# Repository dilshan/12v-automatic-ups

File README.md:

# 12V Uninterruptible Power Supply

This 12V uninterruptible power supply initially designs to drive my fiber optic modem/router. The key reason to build this power supply is to get continuous internet and phone connection during power failures. Core components of this power supply are a constant voltage charger, 12V DC power supply, AC line monitoring unit, and 12V high capacity sealed lead-acid battery. The entire system designs using locally available components.

The charging circuit of this system builds around using the popular *[LM350](https://www.ti.com/lit/ds/snvs772b/snvs772b.pdf)* voltage regulator. This regulator calibrates to provide both 14.4V fast charging and 13.6V trickle charging. Based on the condition of the battery, the MCU will determine the appropriate charging mode.

At the online state, the *[LM2576-12](https://www.ti.com/lit/ds/symlink/lm2576.pdf)* switching regulator provides 12V output to the driving system. (in my arrangement, a fiber optic router).

The *[PIC16F688](http://ww1.microchip.com/downloads/en/devicedoc/41203d.pdf)* MCU monitors the AC line and battery to controls the output voltage of the *LM350* regulator and the output relay. The firmware of this MCU written using the *[Microchip XC8](https://www.microchip.com/en-us/development-tools-tools-and-software/mplab-xc-compilers)* compiler, and all the source code and configuration files are available to [download](https://github.com/dilshan/12v-automatic-ups/releases) in this project repository.

The sealed 12V lead-acid battery is the most crucial component of this unit. 12V, 9Ah battery is the most recommended for this system. At the time of this writing, this battery cost around Rs. 3500 (US$ 17.60), and I bought it from a local online store.

In online mode, this system provides 12V output. In offline mode, if it has a fully charged battery, it delivers an output of 12.5V.

This uninterruptible power supply is suitable for appliances that need 12V - 13V input with a maximum of 2A current. With the configuration described above, this system continued to power my *[Huawei HG8245H5](https://carrier.huawei.com/en/products/fixed-network/access/cpe/h-series-products/hg8245h)* fiber optic router for more than 7 hours.

This power supply unit is an open hardware project. All the [schematic](https://github.com/dilshan/12v-automatic-ups/blob/main/design/ups-12v.pdf), [KiCAD PCB design files](https://github.com/dilshan/12v-automatic-ups/tree/main/design), [firmware source codes](https://github.com/dilshan/12v-automatic-ups/tree/main/firmware), and [compiled binaries](https://github.com/dilshan/12v-automatic-ups/releases) are available to download in this repository.

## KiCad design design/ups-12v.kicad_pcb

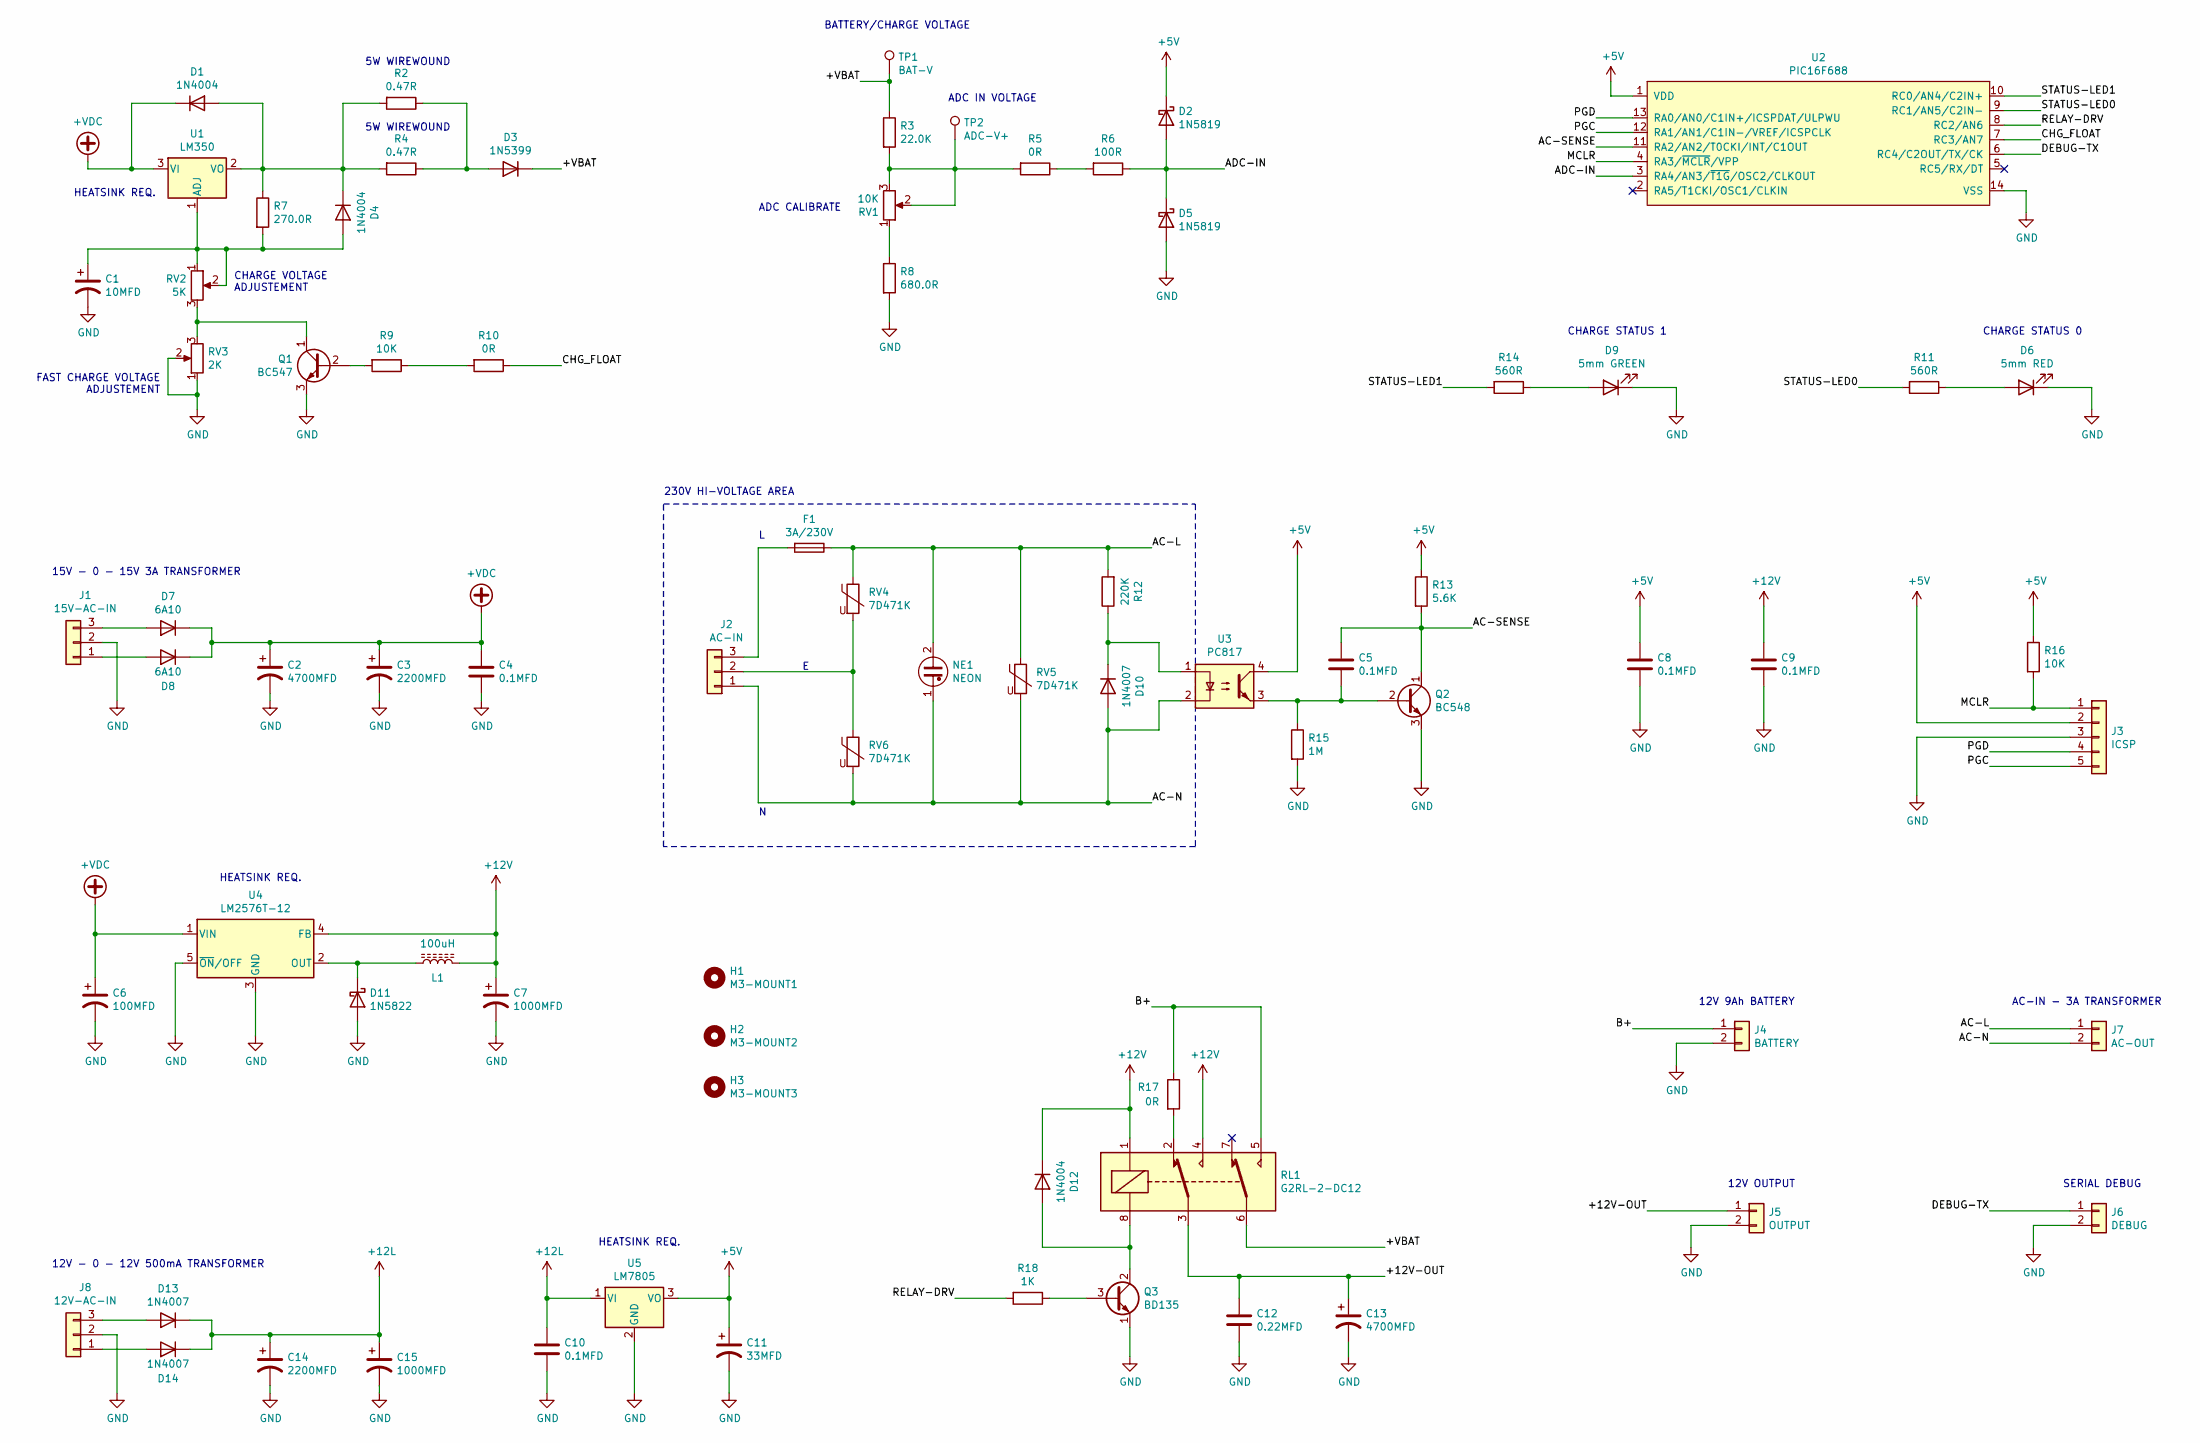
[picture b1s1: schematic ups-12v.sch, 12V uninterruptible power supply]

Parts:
C1: 10MFD; CP_Radial_D5.0mm_P2.00mm
C2, C13: 4700MFD; CP_Radial_D18.0mm_P7.50mm
C3, C14: 2200MFD; CP_Radial_D16.0mm_P7.50mm
C4, C5, C8, C9, C10: 0.1MFD; C_Disc_D10.5mm_W5.0mm_P7.50mm
C6: 100MFD; CP_Radial_D6.3mm_P2.50mm
C7, C15: 1000MFD; CP_Radial_D12.5mm_P5.00mm
C11: 33MFD; CP_Radial_D5.0mm_P2.50mm
C12: 0.22MFD; C_Disc_D11.0mm_W5.0mm_P10.00mm
D1, D4, D12: 1N4004; D_DO-41_SOD81_P10.16mm_Horizontal
D2, D5: 1N5819; D_DO-41_SOD81_P10.16mm_Horizontal
D3: 1N5399; D_DO-41_SOD81_P10.16mm_Horizontal
D6: 5mm RED; PinHeader_1x02_P2.54mm_Vertical
D7, D8: 6A10; D_P600_R-6_P20.00mm_Horizontal
D9: 5mm GREEN; PinHeader_1x02_P2.54mm_Vertical
D10, D13, D14: 1N4007; D_DO-41_SOD81_P10.16mm_Horizontal
D11: 1N5822; D_DO-201AD_P15.24mm_Horizontal
F1: 3A/230V; Fuseholder_Cylinder-5x20mm_Schurter_0031_8201_Horizontal_Op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
H1: M3-MOUNT1; MountingHole_3.2mm_M3
H2: M3-MOUNT2; MountingHole_3.2mm_M3
H3: M3-MOUNT3; MountingHole_3.2mm_M3
J1: 15V-AC-IN; Molex_Sabre_43160-0103_1x03_P7.49mm_Vertical
J2: AC-IN; Molex_Sabre_43160-0103_1x03_P7.49mm_Vertical
J3: ICSP; PinHeader_1x05_P2.54mm_Vertical
J4: BATTERY; Molex_Sabre_43160-0102_1x02_P7.49mm_Vertical
J5: OUTPUT; Molex_Sabre_43160-0102_1x02_P7.49mm_Vertical
J6: DEBUG; PinHeader_1x02_P2.54mm_Vertical
J7: AC-OUT; Molex_Sabre_43160-0102_1x02_P7.49mm_Vertical
J8: 12V-AC-IN; Molex_Sabre_43160-0103_1x03_P7.49mm_Vertical
L1: 100uH; L_Toroid_Vertical_L13.0mm_W6.5mm_P5.60mm
NE1: NEON; Fuse_Bourns_MF-RG300
Q1: BC547; TO-92_HandSolder
Q2: BC548; TO-92_HandSolder
Q3: BD135; TO-126-3_Vertical
R2, R4: 0.47R; R_Axial_Power_L25.0mm_W6.4mm_P27.94mm
R3: 22.0K; R_Axial_DIN0207_L6.3mm_D2.5mm_P10.16mm_Horizontal
R5: 0R; R_Axial_DIN0207_L6.3mm_D2.5mm_P15.24mm_Horizontal
R6: 100R; R_Axial_DIN0207_L6.3mm_D2.5mm_P15.24mm_Horizontal
R7: 270.0R; R_Axial_DIN0207_L6.3mm_D2.5mm_P10.16mm_Horizontal
R8: 680.0R; R_Axial_DIN0207_L6.3mm_D2.5mm_P10.16mm_Horizontal
R9, R16: 10K; R_Axial_DIN0207_L6.3mm_D2.5mm_P10.16mm_Horizontal
R10, R17: 0R; R_Axial_DIN0207_L6.3mm_D2.5mm_P10.16mm_Horizontal
R11, R14: 560R; R_Axial_DIN0207_L6.3mm_D2.5mm_P10.16mm_Horizontal
R12: 220K; R_Axial_DIN0207_L6.3mm_D2.5mm_P10.16mm_Horizontal
R13: 5.6K; R_Axial_DIN0207_L6.3mm_D2.5mm_P10.16mm_Horizontal
R15: 1M; R_Axial_DIN0207_L6.3mm_D2.5mm_P10.16mm_Horizontal
R18: 1K; R_Axial_DIN0207_L6.3mm_D2.5mm_P10.16mm_Horizontal
RL1: G2RL-2-DC12; Relay_DPDT_Omron_G2RL
RV1: 10K; Potentiometer_Runtron_RM-065_Vertical
RV2: 5K; Potentiometer_Runtron_RM-065_Vertical
RV3: 2K; Potentiometer_Runtron_RM-065_Vertical
RV4, RV5, RV6: 7D471K; RV_Disc_D9mm_W4mm_P5mm
TP1: BAT-V; TestPoint_Plated_Hole_D2.0mm
TP2: ADC-V+; TestPoint_Plated_Hole_D2.0mm
U1: LM350; TO-220-3_Vertical
U2: PIC16F688; DIP-14_W7.62mm_LongPads
U3: PC817; DIP-4_W7.62mm
U4: LM2576T-12; TO-220-5_Vertical
U5: LM7805; TO-220-3_Vertical

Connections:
+5V: C8.1, C11.1, D2.1 (K), J3.2, R13.1, R16.1, U2.1 (VDD), U3.4, U5.3 (VO)
+12L: C10.1, C14.1, C15.1, D13.1 (K), D14.1 (K), U5.1 (VI)
+12V: C7.1, C9.1, D12.1 (K), L1.2, RL1.1, RL1.4, U4.4 (FB)
+VDC: C2.1, C3.1, C4.1, C6.1, D1.1 (K), D7.1 (K), D8.1 (K), U1.3 (VI), U4.1 (VIN)
/+12V-OUT: C12.1, C13.1, J5.1, RL1.3
/+VBAT: D3.1 (K), R3.1, RL1.6, TP1.1
/AC-L: F1.1, J7.1, NE1.2, R12.2, RV4.1, RV5.1
/AC-N: D10.2 (A), J2.1, J7.2, NE1.1, RV5.2, RV6.2, U3.2
/AC-SENSE: C5.1, Q2.1 (C), R13.2, U2.11 (RA2/AN2/T0CKI/INT/C1OUT)
/ADC-IN: D2.2 (A), D5.1 (K), R6.1, U2.3 (RA4/AN3/~T1G~/OSC2/CLKOUT)
/B+: J4.1, R17.1, RL1.5
/CHG_FLOAT: R10.1, U2.7 (RC3/AN7)
/DEBUG-TX: J6.1, U2.6 (RC4/C2OUT/TX/CK)
/MCLR: J3.1, R16.2, U2.4 (RA3/~MCLR~/VPP)
/PGC: J3.5, U2.12 (RA1/AN1/C1IN-/VREF/ICSPCLK)
/PGD: J3.4, U2.13 (RA0/AN0/C1IN+/ICSPDAT/ULPWU)
/RELAY-DRV: R18.2, U2.8 (RC2/AN6)
/STATUS-LED0: R11.2, U2.9 (RC1/AN5/C2IN-)
/STATUS-LED1: R14.2, U2.10 (RC0/AN4/C2IN+)
GND: C1.2, C2.2, C3.2, C4.2, C6.2, C7.2, C8.2, C9.2, C10.2, C11.2, C12.2, C13.2, C14.2, C15.2, D5.2 (A), D6.1 (K), D9.1 (K), D11.2 (A), J1.2, J3.3, J4.2, J5.2, J6.2, J8.2, Q1.3 (E), Q2.3 (E), Q3.1 (E), R8.2, R15.2, RV3.1, RV3.2, U2.14 (VSS), U4.3 (GND), U4.5 (~ON~/OFF), U5.2 (GND)
unnamed: C1.1, D4.2 (A), R7.2, RV2.1, RV2.2, U1.1 (ADJ)
unnamed: C5.2, Q2.2 (B), R15.1, U3.3
unnamed: D1.2 (A), D4.1 (K), R2.2, R4.2, R7.1, U1.2 (VO)
unnamed: D3.2 (A), R2.1, R4.1
unnamed: D6.2 (A), R11.1
unnamed: D7.2 (A), J1.3
unnamed: D8.2 (A), J1.1
unnamed: D9.2 (A), R14.1
unnamed: D10.1 (K), R12.1, U3.1
unnamed: D11.1 (K), L1.1, U4.2 (OUT)
unnamed: D12.2 (A), Q3.2 (C), RL1.8
unnamed: D13.2 (A), J8.3
unnamed: D14.2 (A), J8.1
unnamed: F1.2, J2.3
unnamed: J2.2, RV4.2, RV6.1
unnamed: Q1.1 (C), RV2.3, RV3.3
unnamed: Q1.2 (B), R9.2
unnamed: Q3.3 (B), R18.1
unnamed: R3.2, R5.2, RV1.2, RV1.3, TP2.1
unnamed: R5.1, R6.2
unnamed: R8.1, RV1.1
unnamed: R9.1, R10.2
unnamed: R17.2, RL1.2

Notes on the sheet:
CHARGE VOLTAGE ADJUSTEMENT
FAST CHARGE VOLTAGE ADJUSTEMENT
ADC CALIBRATE
BATTERY/CHARGE VOLTAGE
ADC IN VOLTAGE
15V - 0 - 15V 3A TRANSFORMER
HEATSINK REQ.
CHARGE STATUS 0
CHARGE STATUS 1
12V 9Ah BATTERY
SERIAL DEBUG
12V OUTPUT
5W WIREWOUND
230V HI-VOLTAGE AREA
AC-IN - 3A TRANSFORMER
12V - 0 - 12V 500mA TRANSFORMER

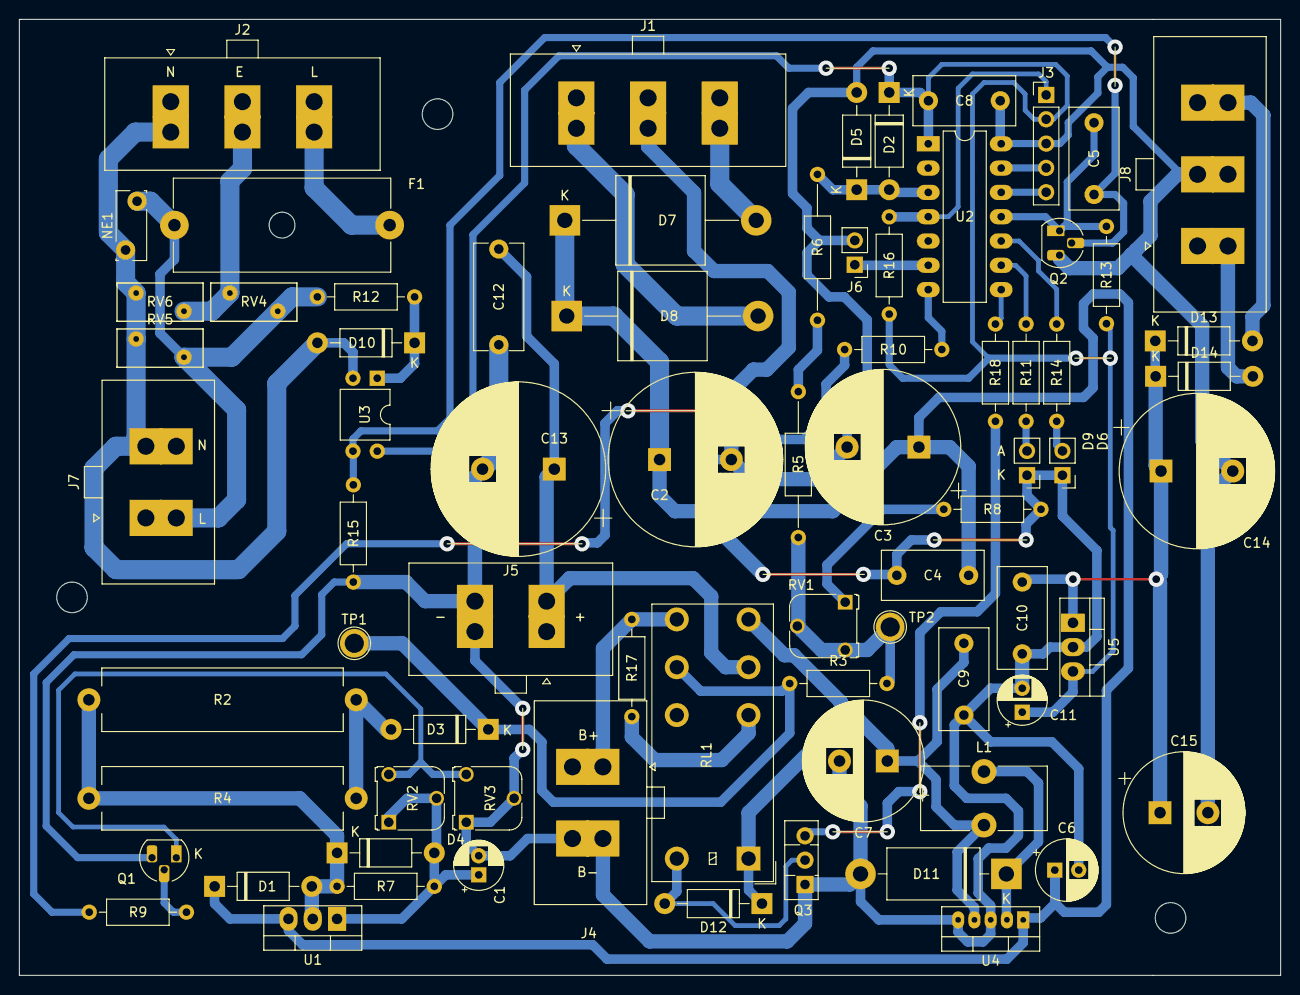
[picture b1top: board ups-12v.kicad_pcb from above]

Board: 2 copper layers, 131.8 x 99.9 mm, 77 parts (0 on the bottom side), 43 nets.

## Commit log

2021-06-27 Initial version of 12V UPS design files and source codes.
2021-06-27 Fix typos in readme file and BOM file.
2021-06-27 Add image of prototype build into the readme file.
2021-06-27 Add block diagram of the system into the readme file.
2021-06-27 Add repository links to the readme.md file.
2021-06-28 Add LibreOffice Draw version of the block diagram files.

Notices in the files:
design/ups-12v.kicad_pcb:
This work is licensed under a Creative Commons Attribution 4.0 International License.
